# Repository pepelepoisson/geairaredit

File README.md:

***
This repo contains files about a project called GeaiRareDit. It is all about building a small hand-held game starting with classical SimonSays game. This is very much WIP and shall be updated as project evolves.
***
***

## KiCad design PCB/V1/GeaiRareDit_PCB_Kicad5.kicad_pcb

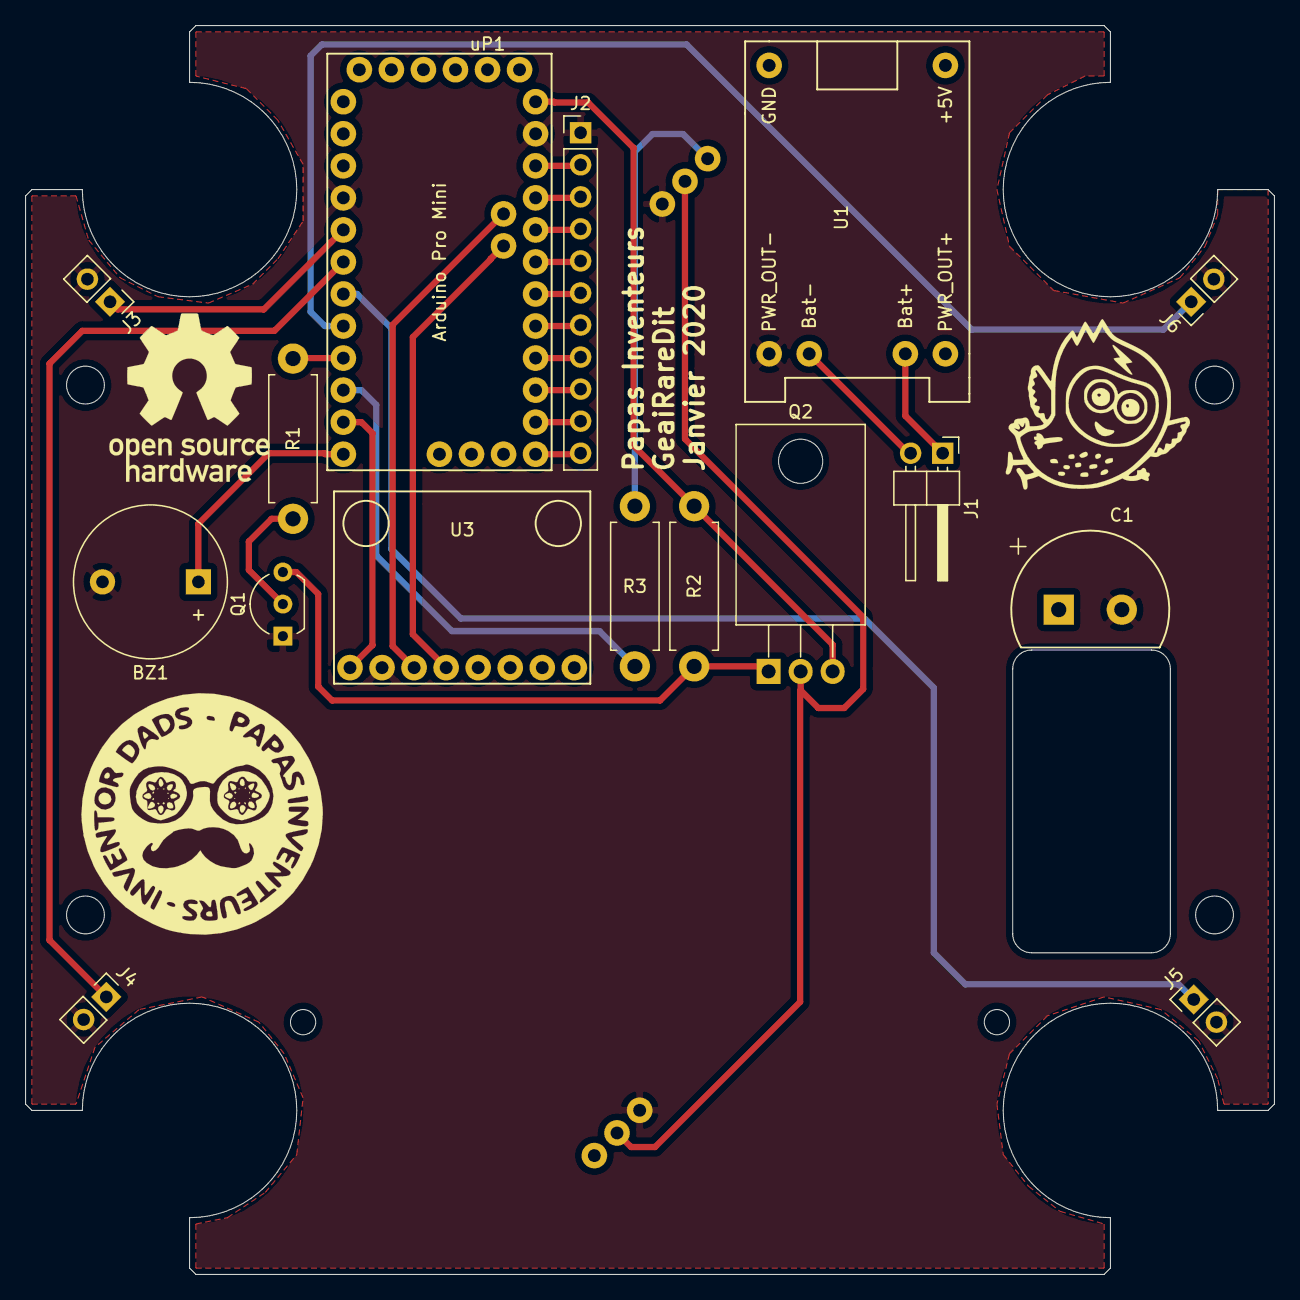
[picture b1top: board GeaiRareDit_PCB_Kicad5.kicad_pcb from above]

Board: 2 copper layers, 99.0 x 99.0 mm, 17 parts (1 on the bottom side), 28 nets.

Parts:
BZ1: Buzzer; Buzzer_12x9.5RM7.6
C1: 1000microF; Edge_CP_Radial_D12.5mm_P5.00mm
J1: LIPO_IN; PinHeader_1x02_P2.54mm_Horizontal
J2: Conn_01x11; PinHeader_1x11_P2.54mm_Vertical
J3: Conn_SW1; PinHeader_1x02_P2.54mm_Vertical
J4: Conn_SW2; PinHeader_1x02_P2.54mm_Vertical
J5: Conn_SW3; PinHeader_1x02_P2.54mm_Vertical
J6: Conn_SW4; PinHeader_1x02_P2.54mm_Vertical
Q1: 2N3904; TO-92L_Inline_Wide
Q2: NPD6020P; TO-220-3_Horizontal_TabDown
R1: 10K; R_Axial_DIN0411_L9.9mm_D3.6mm_P12.70mm_Horizontal
R2: 10k; R_Axial_DIN0411_L9.9mm_D3.6mm_P12.70mm_Horizontal
R3: 470; R_Axial_DIN0411_L9.9mm_D3.6mm_P12.70mm_Horizontal
U1: LiPo_Mngmt_Board; LiPo_Mngmt_Board_Big_Holes
U2: WS2812B_8x8_matrix; WS2812B_8x8_CJMCU_Matrix
U3: ITG_MPU6050; ITG_MPU_6050_big_holes
uP1: ARDUPROMINI_pins_on_4_sides; ArduinoProMini_pins_on_4_sides_big_holes

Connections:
+BATT: C1.1, Q2.3, R2.2, U1.4, uP1.19
/3.3V: J2.3, uP1.22
/A0: J2.7, uP1.26
/A1: J2.6, uP1.25
/A2: J2.5, uP1.24
/A3: J2.4, uP1.23
/BUZZER: BZ1.1, uP1.18
/D2: J3.1, uP1.11
/D3: J4.1, uP1.12
/D4: J5.1, uP1.13
/D5: J6.1, uP1.14
/D10: J2.11, uP1.30
/D11: J2.10, uP1.29
/D12: J2.9, uP1.28
/D13: J2.8, uP1.27
/I2C_SCL: U3.3, uP1.31
/I2C_SDA: U3.4, uP1.32
/LIPO+: J1.1, U1.1
/LIPO-: J1.2, U1.2
/MOSFET_CTRL: R1.2, uP1.15
/MPU_VCC: U3.1, uP1.17
/RESET: J2.2, uP1.21
/WS2812B_DATA_IN: R3.1, uP1.16
GND: BZ1.2, C1.2, J2.1, J3.2, J4.2, J5.2, J6.2, Q1.1, U1.3, U2.2, U3.2, uP1.10, uP1.20
unnamed: Q1.2, R1.1
unnamed: Q1.3, Q2.1, R2.1
unnamed: Q2.2, U2.1
unnamed: R3.2, U2.3

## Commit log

2020-01-23 Added first version of PCB and CAD designs
2020-12-04 Added several packaging CAD versions and first code configured for Arduino IDE rather than ATOM PlatformIO due to compilation issues
2020-12-10 Completed CAD V4 - Corresponds @99% to first 3 units made
2020-12-16 Cleanup after R1.0 release
